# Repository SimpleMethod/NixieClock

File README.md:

# NixieClock
Simple Nixie clock without multiplexing

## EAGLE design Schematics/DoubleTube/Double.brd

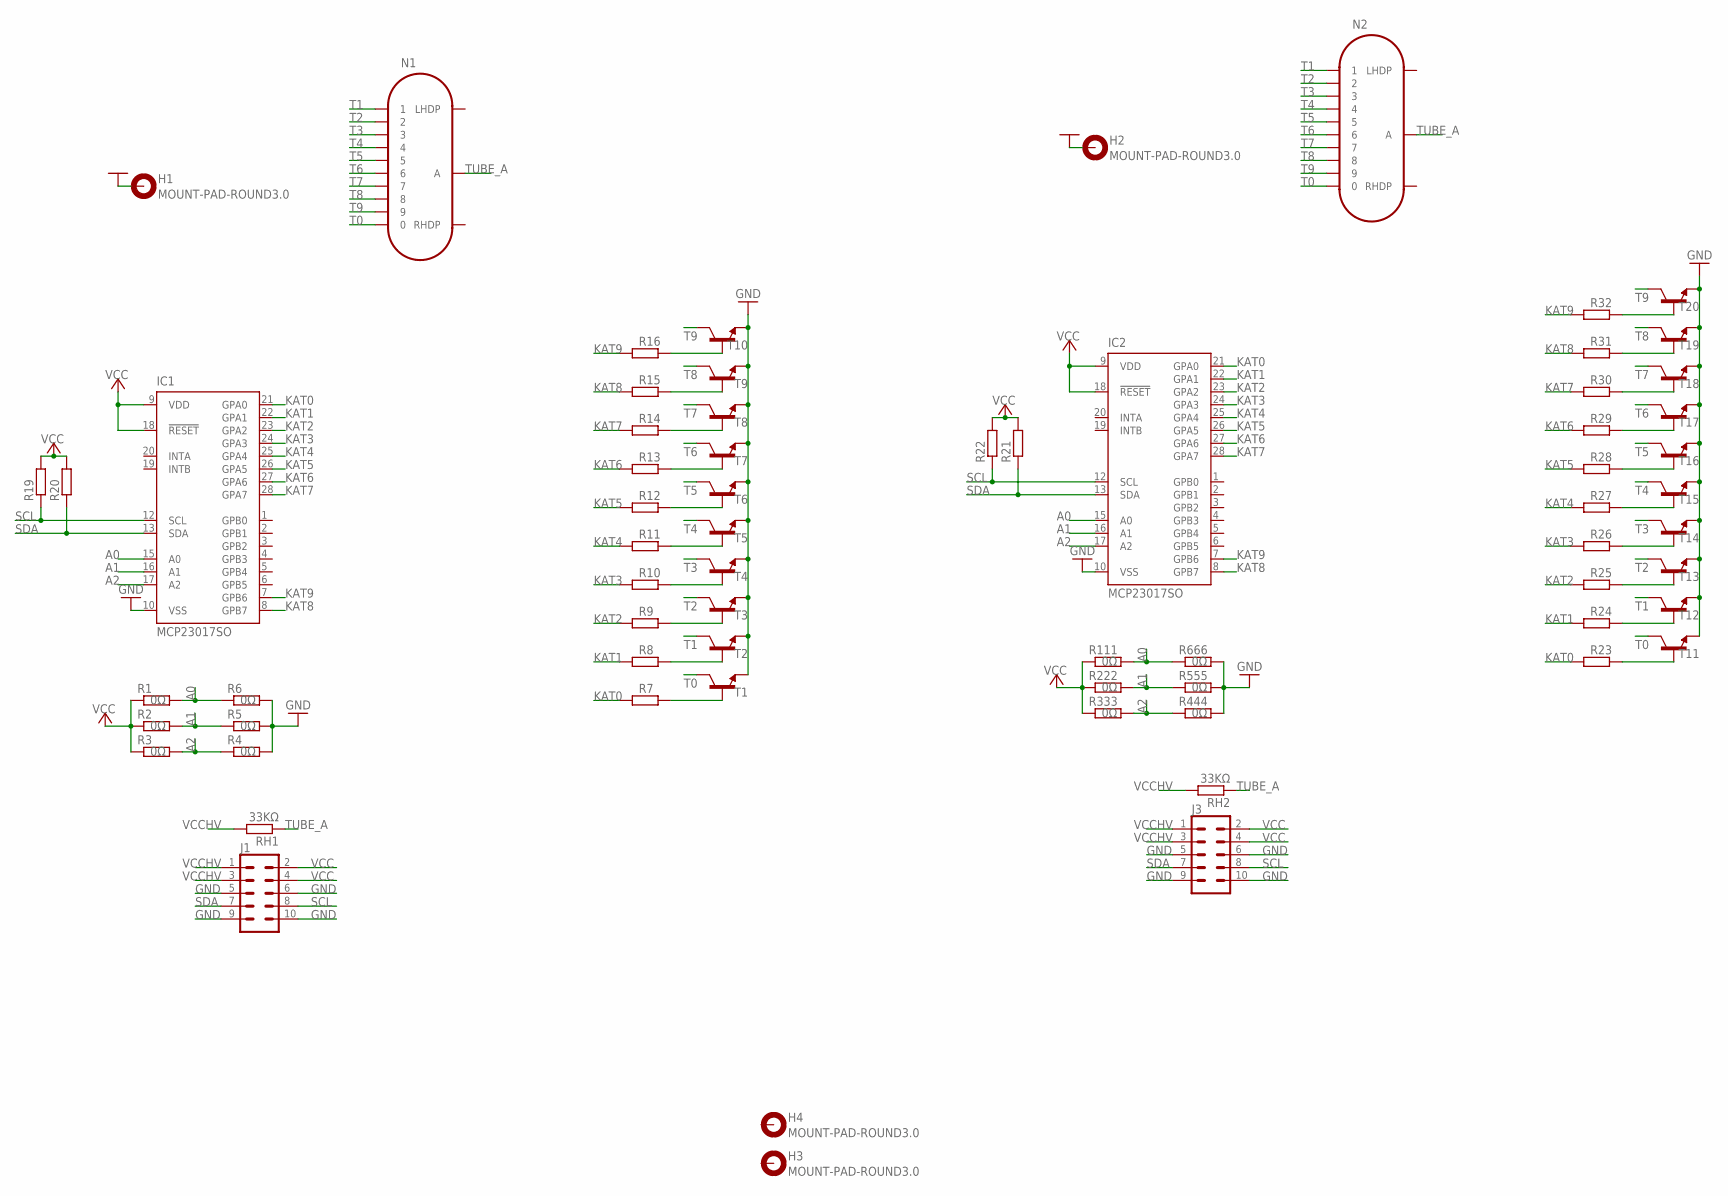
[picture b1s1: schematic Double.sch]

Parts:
H1, H2, H3, H4: MOUNT-PAD-ROUND3.0; 3,0-PAD
IC1, IC2: MCP23017SO; SO28W
J1, J3: CONN_05X2PTH; 2X5
N1, N2: IN-14
R1, R2, R3, R4, R5, R6, R111, R222, R333, R444, R555, R666: 0Ω; R1206
R7, R8, R9, R10, R11, R12, R13, R14, R15, R16, R19, R20, R21, R22, R23, R24, R25, R26, R27, R28, R29, R30, R31, R32: R-EU_R1206; R1206
RH1, RH2: 33KΩ; 0207/15
T1, T2, T3, T4, T5, T6, T7, T8, T9, T10, T11, T12, T13, T14, T15, T16, T17, T18, T19, T20: MMBTA42LT1-NPN-SOT23-BEC; SOT23-BEC

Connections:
A0: IC1.15 (A0), IC2.15 (A0), R1.2, R6.1, R111.2, R666.1
A1: IC1.16 (A1), IC2.16 (A1), R2.2, R5.1, R222.2, R555.1
A2: IC1.17 (A2), IC2.17 (A2), R3.2, R4.1, R333.2, R444.1
GND: H1.B3,0, H2.B3,0, IC1.10 (VSS), IC2.10 (VSS), J1.5, J1.6, J1.9, J1.10, J3.5, J3.6, J3.9, J3.10, R4.2, R5.2, R6.2, R444.2, R555.2, R666.2, T1.E, T2.E, T3.E, T4.E, T5.E, T6.E, T7.E, T8.E, T9.E, T10.E, T11.E, T12.E, T13.E, T14.E, T15.E, T16.E, T17.E, T18.E, T19.E, T20.E
KAT0: IC1.21 (GPA0), IC2.21 (GPA0), R7.1, R23.1
KAT1: IC1.22 (GPA1), IC2.22 (GPA1), R8.1, R24.1
KAT2: IC1.23 (GPA2), IC2.23 (GPA2), R9.1, R25.1
KAT3: IC1.24 (GPA3), IC2.24 (GPA3), R10.1, R26.1
KAT4: IC1.25 (GPA4), IC2.25 (GPA4), R11.1, R27.1
KAT5: IC1.26 (GPA5), IC2.26 (GPA5), R12.1, R28.1
KAT6: IC1.27 (GPA6), IC2.27 (GPA6), R13.1, R29.1
KAT7: IC1.28 (GPA7), IC2.28 (GPA7), R14.1, R30.1
KAT8: IC1.8 (GPB7), IC2.8 (GPB7), R15.1, R31.1
KAT9: IC1.7 (GPB6), IC2.7 (GPB6), R16.1, R32.1
unnamed: R7.2, T1.B
unnamed: R16.2, T10.B
unnamed: R15.2, T9.B
unnamed: R14.2, T8.B
unnamed: R13.2, T7.B
unnamed: R12.2, T6.B
unnamed: R11.2, T5.B
unnamed: R10.2, T4.B
unnamed: R9.2, T3.B
unnamed: R8.2, T2.B
unnamed: R23.2, T11.B
unnamed: R32.2, T20.B
unnamed: R31.2, T19.B
unnamed: R30.2, T18.B
unnamed: R29.2, T17.B
unnamed: R28.2, T16.B
unnamed: R27.2, T15.B
unnamed: R26.2, T14.B
unnamed: R25.2, T13.B
unnamed: R24.2, T12.B
SCL: IC1.12 (SCL), IC2.12 (SCL), J1.8, J3.8, R19.1, R22.1
SDA: IC1.13 (SDA), IC2.13 (SDA), J1.7, J3.7, R20.1, R21.1
T0: N1.0, N2.0, T1.C, T11.C
T1: N1.1, N2.1, T2.C, T12.C
T2: N1.2, N2.2, T3.C, T13.C
T3: N1.3, N2.3, T4.C, T14.C
T4: N1.4, N2.4, T5.C, T15.C
T5: N1.5, N2.5, T6.C, T16.C
T6: N1.6, N2.6, T7.C, T17.C
T7: N1.7, N2.7, T8.C, T18.C
T8: N1.8, N2.8, T9.C, T19.C
T9: N1.9, N2.9, T10.C, T20.C
TUBE_A: N1.A, N2.A, RH1.1, RH2.1
VCC: IC1.9 (VDD), IC1.18 (!RESET), IC2.9 (VDD), IC2.18 (!RESET), J1.2, J1.4, J3.2, J3.4, R1.1, R2.1, R3.1, R19.2, R20.2, R21.2, R22.2, R111.1, R222.1, R333.1
VCCHV: J1.1, J1.3, J3.1, J3.3, RH1.2, RH2.2

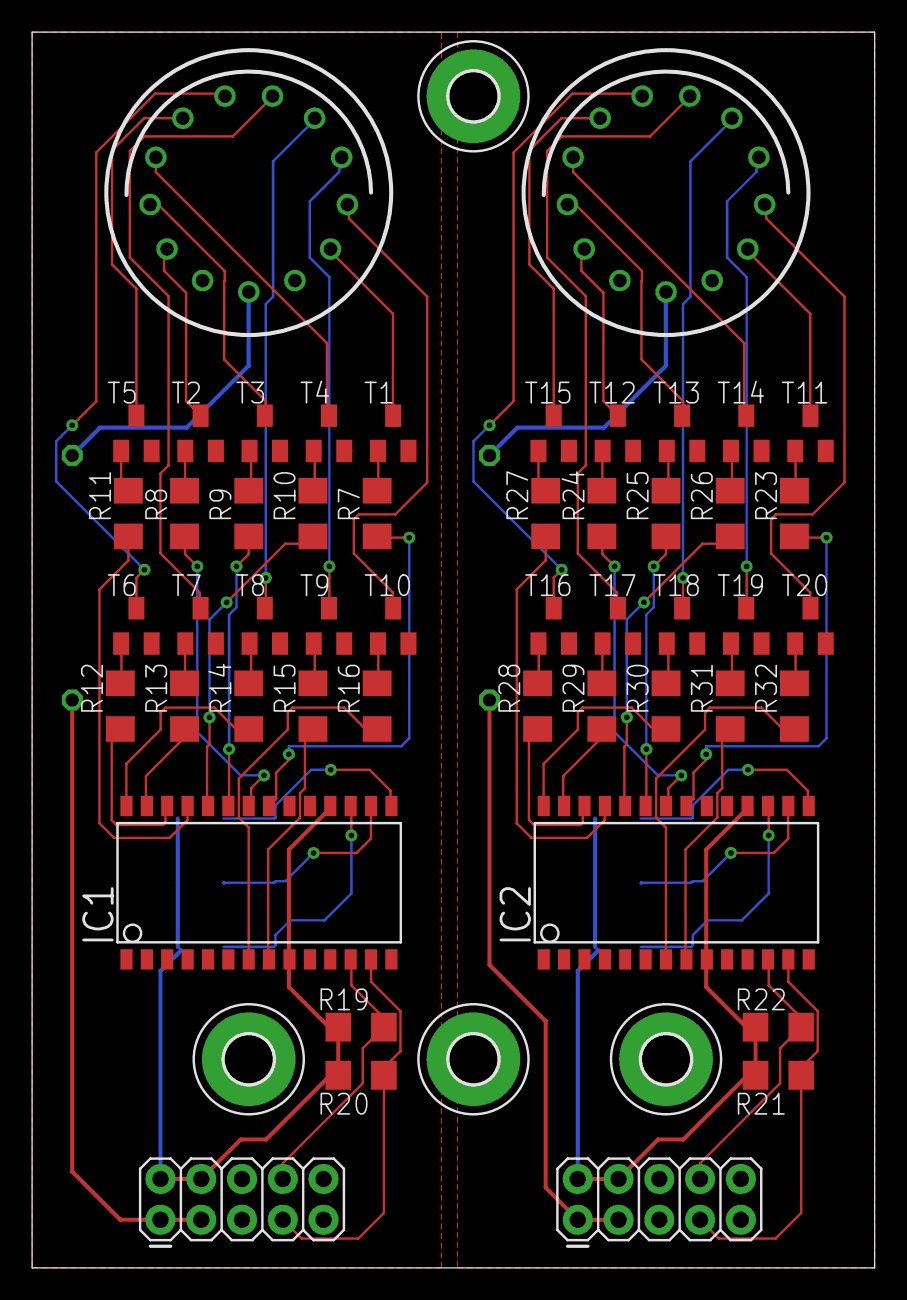
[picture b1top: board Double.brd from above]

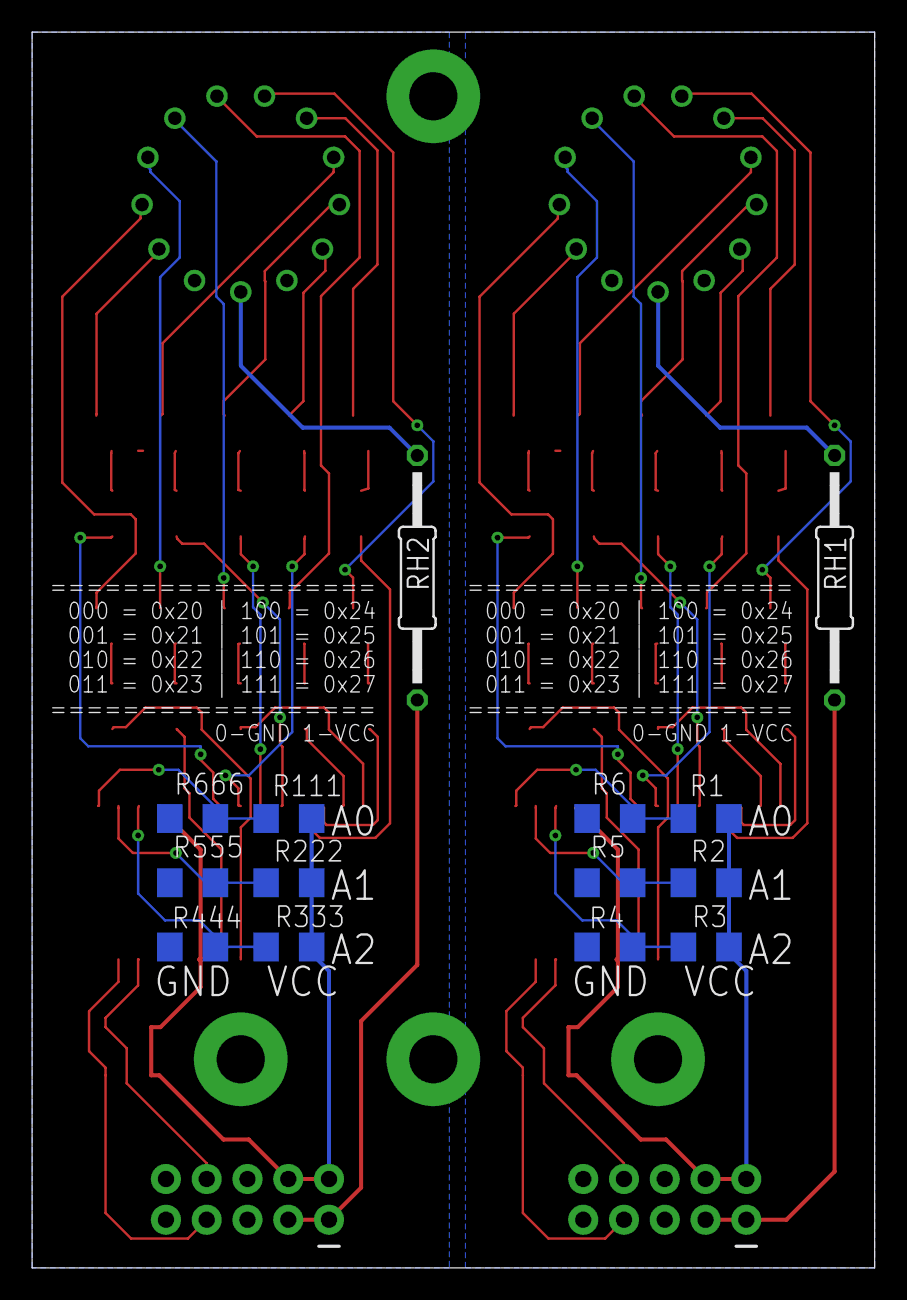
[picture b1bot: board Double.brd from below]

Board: 2 copper layers, 52.5 x 77.0 mm, 68 parts (14 on the bottom side), 49 nets.

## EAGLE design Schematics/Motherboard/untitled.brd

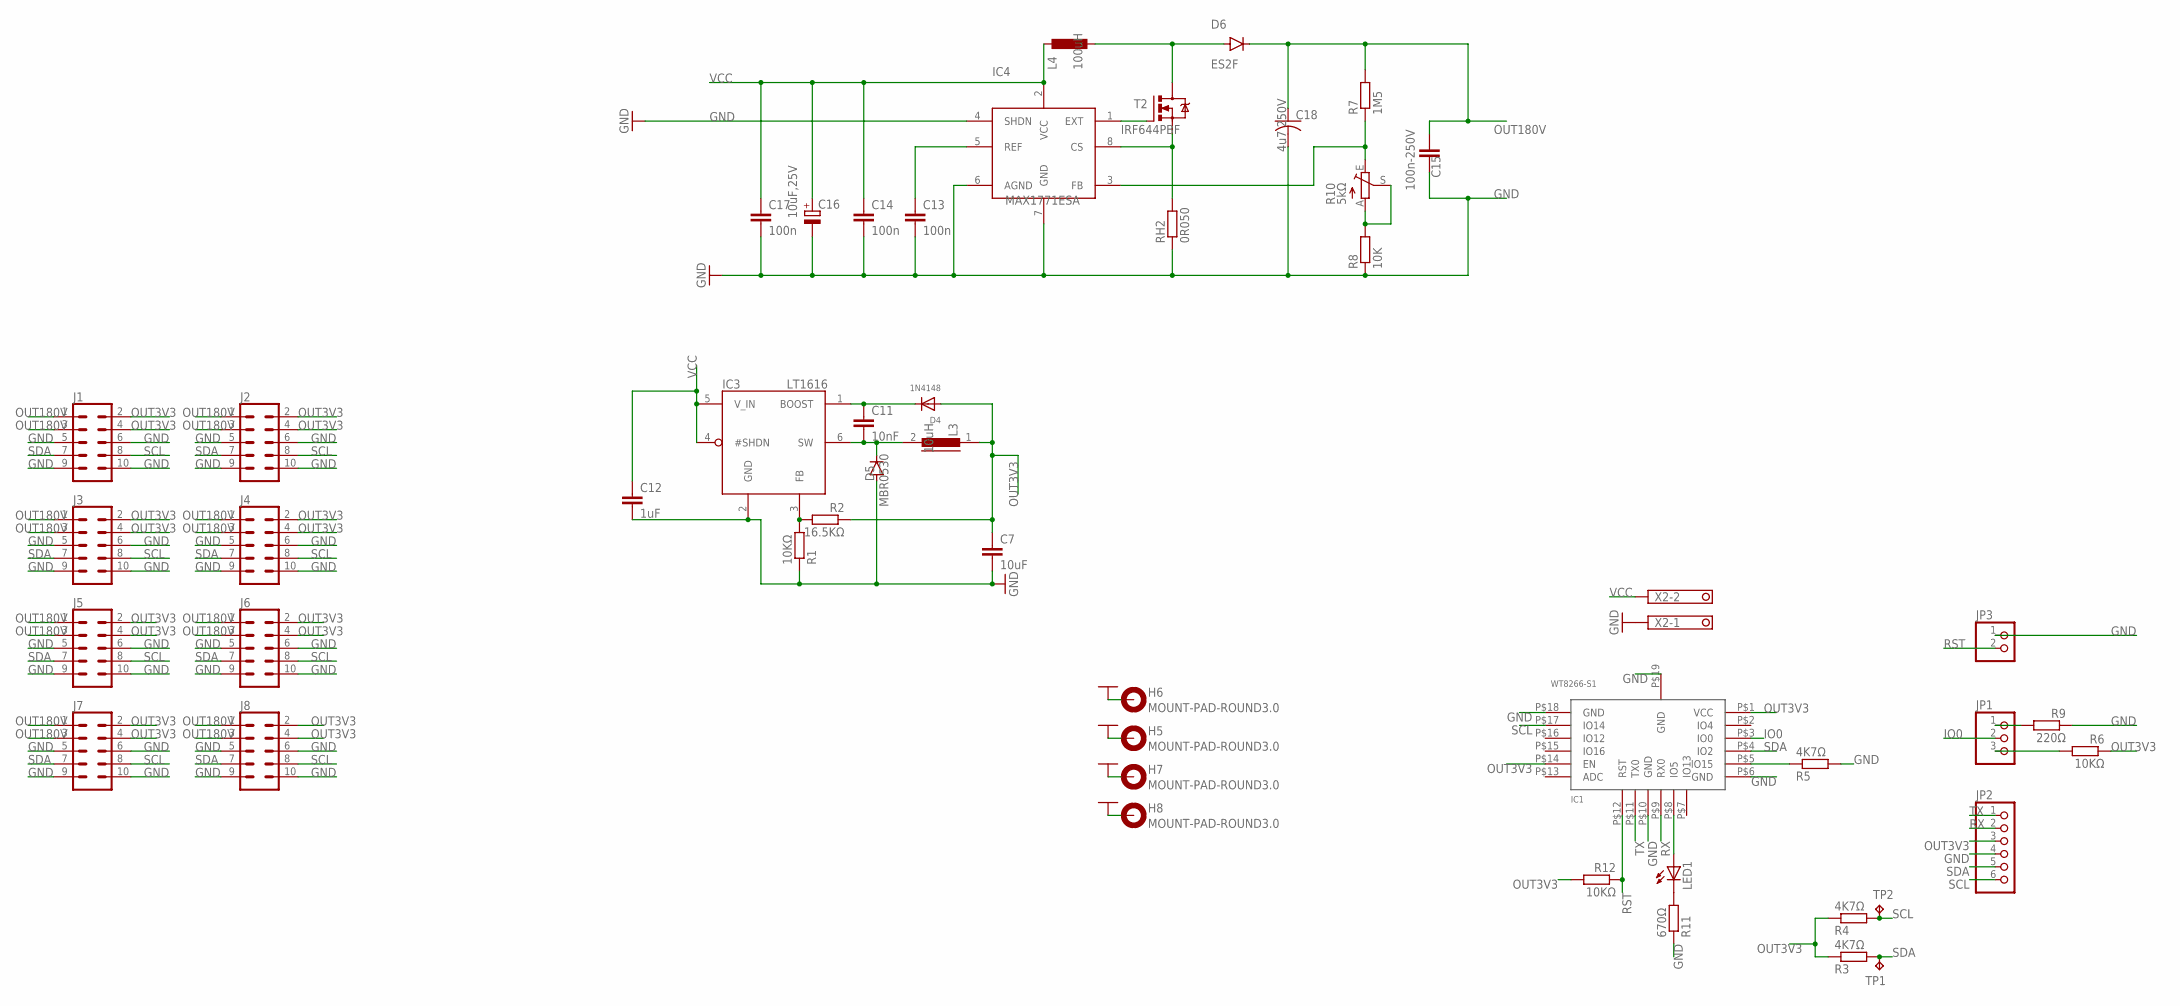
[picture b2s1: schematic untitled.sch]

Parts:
C7: 10uF; C1206
C11: 10nF; C1206
C12: 1uF; C1206
C13, C14, C17: 100n; C1206
C15: 100n-250V; C2420
C16: 10uF,25V; C-EIA-7343
C18: 4u7 250V; CAP_RADIAL_5MM
D4: 1N4148; DO-1N4148
D5: MBR0530; SOD123
D6: ES2F; SMC
H5, H6, H7, H8: MOUNT-PAD-ROUND3.0; 3,0-PAD
IC1: WT8266-S1
IC3: LT1616; SOT23-6
IC4: MAX1771ESA; SO-8
J1, J2, J3, J4, J5, J6, J7, J8: CONN_05X2PTH; 2X5
JP1: PINHD-1X3; 1X03
JP2: PINHD-1X6; 1X06
JP3: PINHD-1X2; 1X02
L3: 10uH; 82114R
L4: 100uH; TJ3-U1
LED1: LED3MM
R1, R6, R12: 10KΩ; R1206
R2: 16.5KΩ; R0805
R3, R4, R5: 4K7Ω; R1206
R7: 1M5; R2512
R8: 10K; R1206
R9: 220Ω; R1206
R10: 5kΩ; RS3
R11: 670Ω; R1206
RH2: 0R050; R2512
T2: IRF644PBF; TO220BV
TP1, TP2: TPTP18R; TP18R
X2: TERMINAL-BLOCK-3.5MM-2-PIN-LONG-PAD; TERMINAL-BLOCK-2-PIN-3.5MM-LONG-PAD

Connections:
EXT1: IC4.1 (EXT), T2.G
GND: C7.2, C12.2, C13.2, C14.2, C15.P$2 (2), C16.-, C17.2, C18.2, D5.A, H5.B3,0, H6.B3,0, H7.B3,0, H8.B3,0, IC1.P$6 (GND), IC1.P$10 (GND), IC1.P$18 (GND), IC1.P$19 (GND), IC3.2 (GND), IC4.4 (SHDN), IC4.6 (AGND), IC4.7 (GND), J1.5, J1.6, J1.9, J1.10, J2.5, J2.6, J2.9, J2.10, J3.5, J3.6, J3.9, J3.10, J4.5, J4.6, J4.9, J4.10, J5.5, J5.6, J5.9, J5.10, J6.5, J6.6, J6.9, J6.10, J7.5, J7.6, J7.9, J7.10, J8.5, J8.6, J8.9, J8.10, JP2.4, JP3.1, R1.1, R5.2, R8.1, R9.1, R11.1, RH2.1, X2.1
IO0: IC1.P$3 (IO0), JP1.2
unnamed: IC3.3 (FB), R1.2, R2.2
unnamed: IC1.P$5 (IO15), R5.1
unnamed: JP1.1, R9.2
unnamed: C11.2, D5.C, IC3.6 (SW), L3.2
unnamed: C11.1, D4.C, IC3.1 (BOOST)
unnamed: IC4.3 (FB), R7.1, R10.E
unnamed: D6.A, L4.2, T2.D
unnamed: JP1.3, R6.2
unnamed: C13.1, IC4.5 (REF)
unnamed: R8.2, R10.A, R10.S
unnamed: IC4.8 (CS), RH2.2, T2.S
unnamed: IC1.P$8 (IO5), LED1.A
unnamed: LED1.K (C), R11.2
OUT3V3: C7.1, D4.A, IC1.P$1 (VCC), IC1.P$14 (EN), J1.2, J1.4, J2.2, J2.4, J3.2, J3.4, J4.2, J4.4, J5.2, J5.4, J6.2, J6.4, J7.2, J7.4, J8.2, J8.4, JP2.3, L3.1, R2.1, R3.1, R4.1, R6.1, R12.2
OUT180V: C15.P$1 (1), C18.1, D6.C, J1.1, J1.3, J2.1, J2.3, J3.1, J3.3, J4.1, J4.3, J5.1, J5.3, J6.1, J6.3, J7.1, J7.3, J8.1, J8.3, R7.2
RST: IC1.P$12 (RST), JP3.2, R12.1
RX: IC1.P$9 (RX0), JP2.2
SCL: IC1.P$17 (IO14), J1.8, J2.8, J3.8, J4.8, J5.8, J6.8, J7.8, J8.8, JP2.6, R4.2, TP2.TP
SDA: IC1.P$4 (IO2), J1.7, J2.7, J3.7, J4.7, J5.7, J6.7, J7.7, J8.7, JP2.5, R3.2, TP1.TP
TX: IC1.P$11 (TX0), JP2.1
VCC: C12.1, C14.1, C16.+, C17.1, IC3.4 (#SHDN), IC3.5 (V_IN), IC4.2 (VCC), L4.1, X2.2

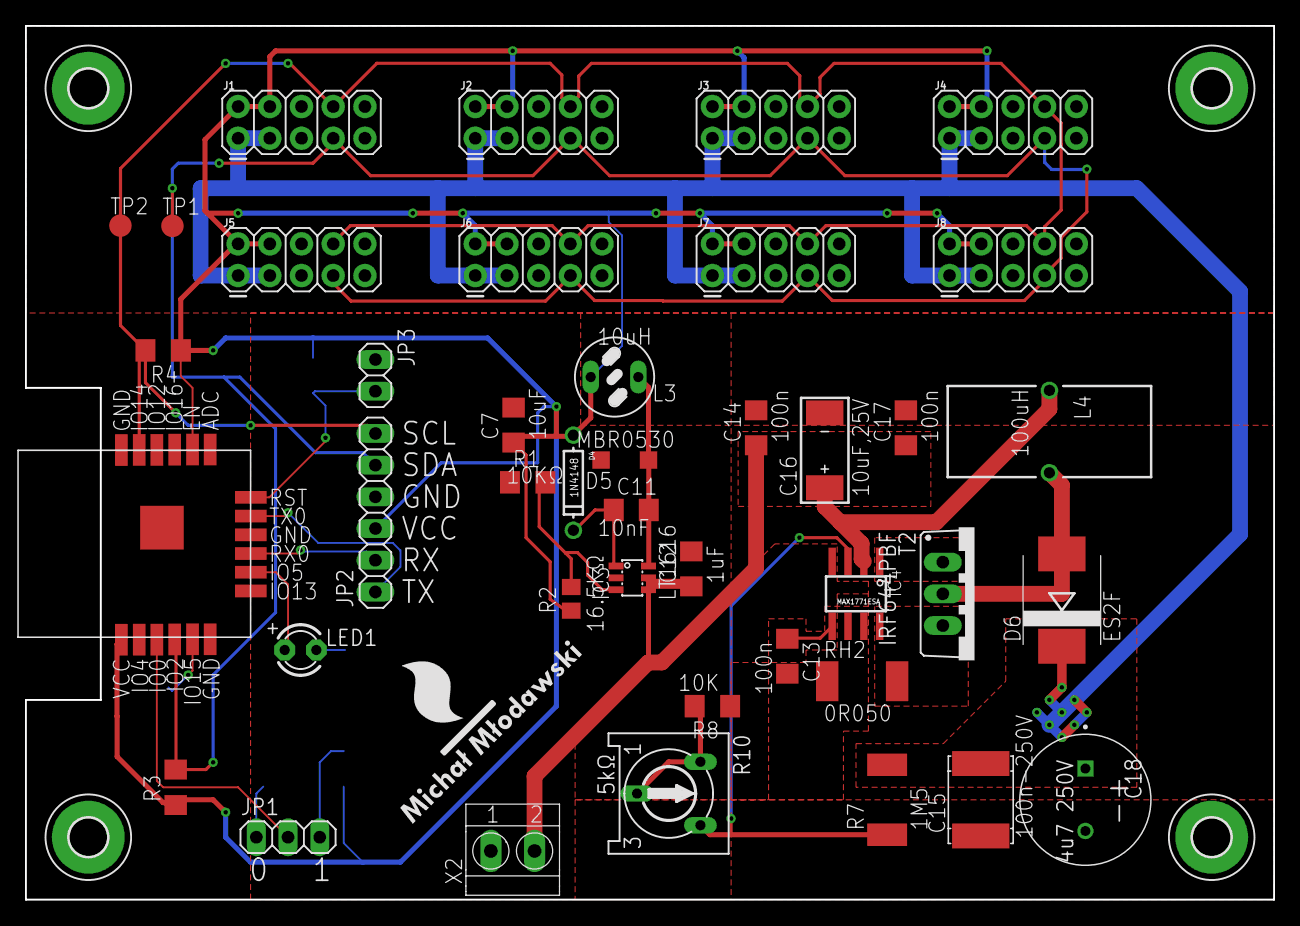
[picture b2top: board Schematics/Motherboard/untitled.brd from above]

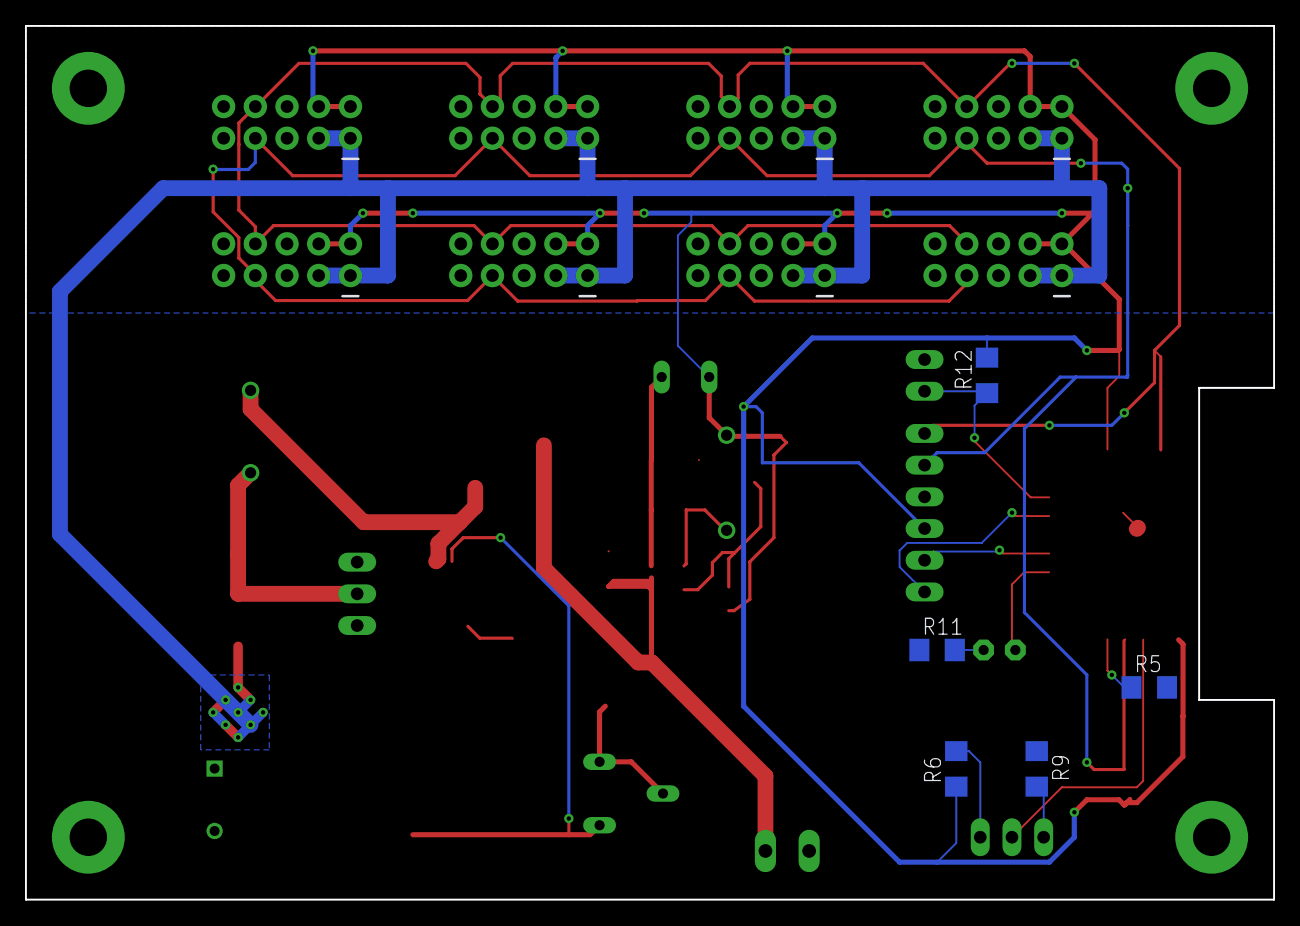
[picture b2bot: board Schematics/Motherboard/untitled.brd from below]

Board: 2 copper layers, 100.0 x 70.0 mm, 50 parts (5 on the bottom side), 24 nets.

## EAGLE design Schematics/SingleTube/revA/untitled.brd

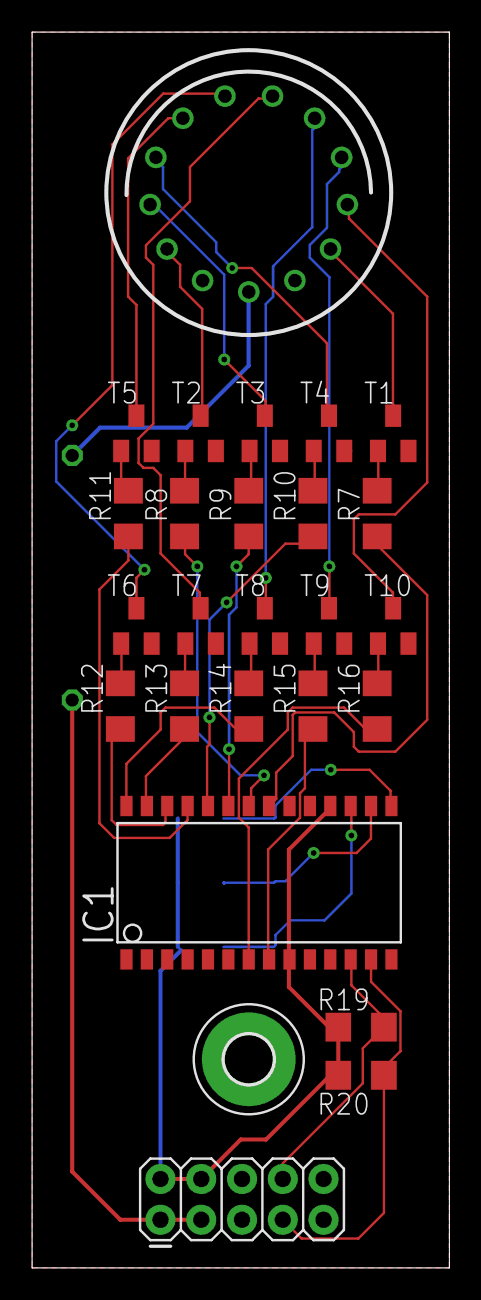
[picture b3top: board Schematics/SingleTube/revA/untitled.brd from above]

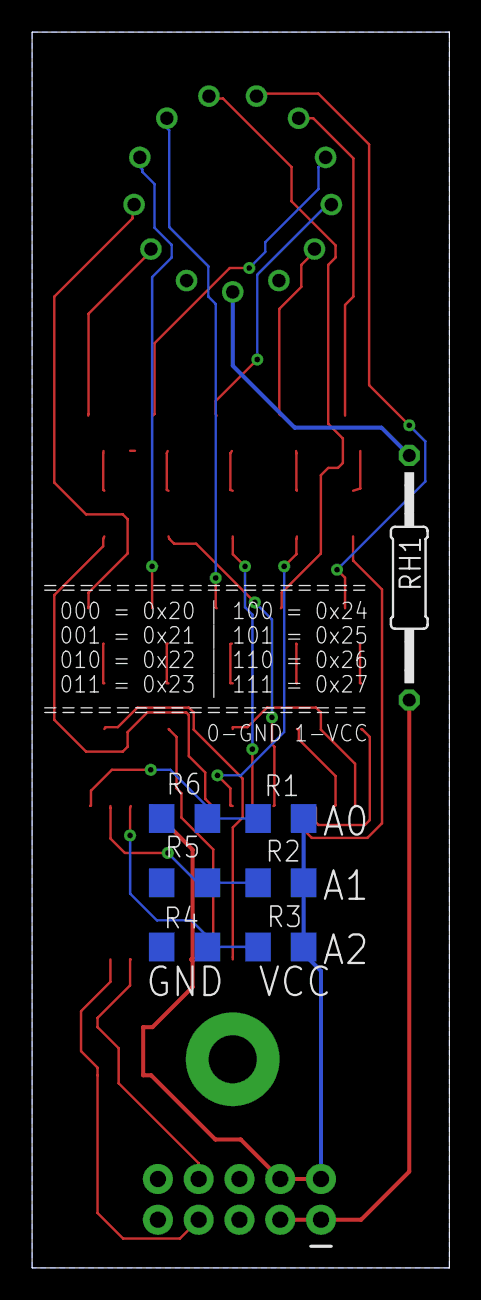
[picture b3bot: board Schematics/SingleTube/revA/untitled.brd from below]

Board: 2 copper layers, 26.0 x 77.0 mm, 33 parts (7 on the bottom side), 39 nets.

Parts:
H1: MOUNT-PAD-ROUND3.0; 3,0-PAD
IC1: MCP23017SO; SO28W
J1: 2X5
N1: IN-14
R1, R2, R3, R4, R5, R6: 0Ω; R1206
R7, R8, R9, R10, R11, R12, R13, R14, R15, R16, R19, R20: R1206
RH1: 33KΩ; 0207/15
T1, T2, T3, T4, T5, T6, T7, T8, T9, T10: SOT23-BEC

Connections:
A0: IC1.15, R1.2, R6.1
A1: IC1.16, R2.2, R5.1
A2: IC1.17, R3.2, R4.1
GND: H1.B3,0, IC1.10, J1.5, J1.6, J1.9, J1.10, R4.2, R5.2, R6.2, T1.E, T2.E, T3.E, T4.E, T5.E, T6.E, T7.E, T8.E, T9.E, T10.E
KAT0: IC1.21, R7.1
KAT1: IC1.22, R8.1
KAT2: IC1.23, R9.1
KAT3: IC1.24, R10.1
KAT4: IC1.25, R11.1
KAT5: IC1.26, R12.1
KAT6: IC1.27, R13.1
KAT7: IC1.28, R14.1
KAT8: IC1.8, R15.1
KAT9: IC1.7, R16.1
unnamed: R7.2, T1.B
unnamed: R16.2, T10.B
unnamed: R15.2, T9.B
unnamed: R14.2, T8.B
unnamed: R13.2, T7.B
unnamed: R12.2, T6.B
unnamed: R11.2, T5.B
unnamed: R10.2, T4.B
unnamed: R9.2, T3.B
unnamed: R8.2, T2.B
SCL: IC1.12, J1.8, R19.1
SDA: IC1.13, J1.7, R20.1
T0: N1.0, T1.C
T1: N1.1, T2.C
T2: N1.2, T3.C
T3: N1.3, T4.C
T4: N1.4, T5.C
T5: N1.5, T6.C
T6: N1.6, T7.C
T7: N1.7, T8.C
T8: N1.8, T9.C
T9: N1.9, T10.C
TUBE_A: N1.A, RH1.1
VCC: IC1.9, IC1.18, J1.2, J1.4, R1.1, R2.1, R3.1, R19.2, R20.2
VCCHV: J1.1, J1.3, RH1.2

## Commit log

2020-08-05 Schematics

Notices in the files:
parts and their libraries:
SparkFun-Connectors: Licensing: Creative Commons ShareAlike 4.0 International - https://creativecommons.org/licenses/by-sa/4.0
